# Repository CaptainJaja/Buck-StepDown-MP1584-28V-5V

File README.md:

# Buck Step-Down MP1584 – 28V vers 5V

Ce projet KiCad implémente un **convertisseur abaisseur (step-down)** basé sur le **MP1584**, capable de convertir une tension d'entrée allant jusqu'à **28V** en une sortie **stabilisée à 5V** avec un courant maximal de **3A**.

Le circuit imprimé a été conçu pour être **compact** et facile à intégrer, avec des dimensions de **24.5 mm × 28 mm**.

---

## 📷 Vues du PCB

### Face top (Top layer)

### Face bottom (Bottom layer)

---

## 📄 Datasheet

La **datasheet du MP1584** est disponible dans le répertoire sous le nom : `MP1584.PDF`

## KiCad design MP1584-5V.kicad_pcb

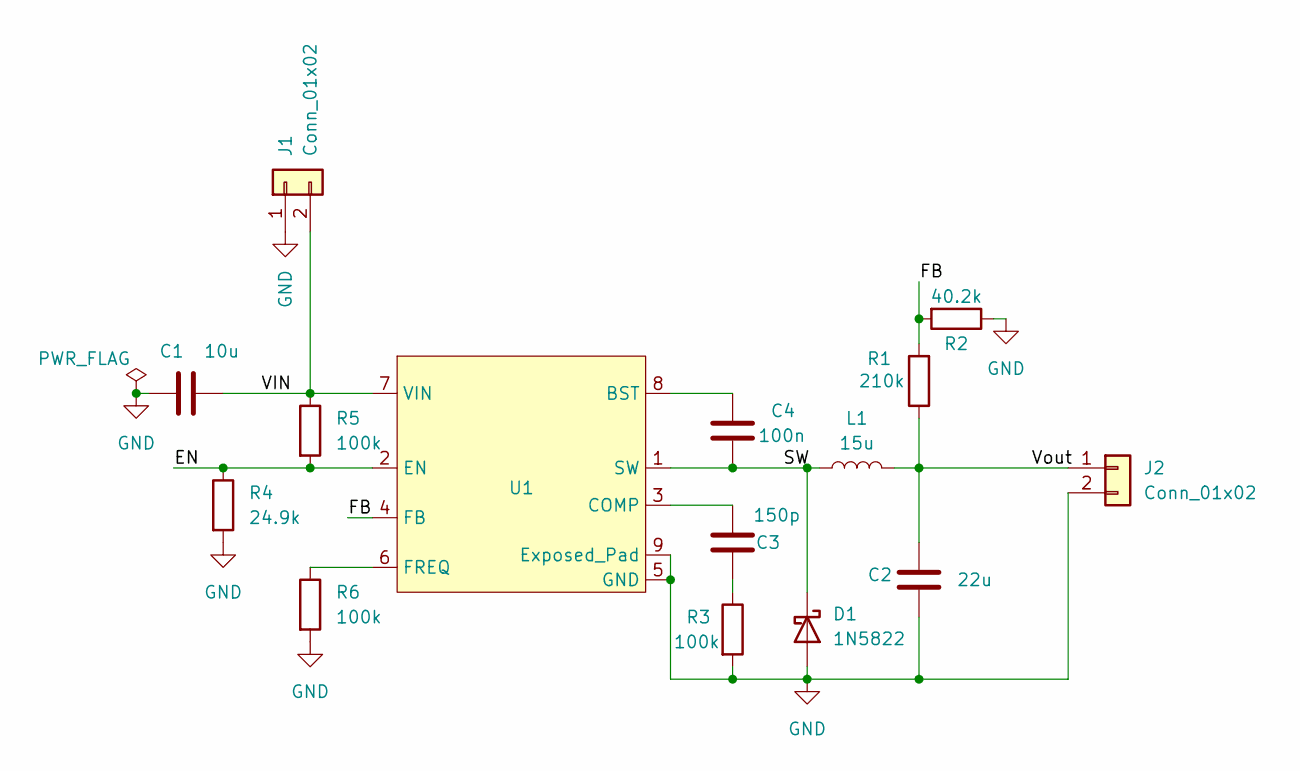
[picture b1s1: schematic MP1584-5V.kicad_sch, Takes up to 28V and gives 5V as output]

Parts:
C1: 10u; C_0603_1608Metric
C2: 22u; C_0805_2012Metric
C3: 150p; C_0603_1608Metric
C4: 100n; C_0603_1608Metric
D1: 1N5822; FSV330AF
J1, J2: Conn_01x02; JST_EH_S2B-EH_1x02_P2.50mm_Horizontal
L1: 15u; CDRH127F-150M
R1: 210k; R_0603_1608Metric
R2: 40.2k; R_0603_1608Metric
R3, R5, R6: 100k; R_0603_1608Metric
R4: 24.9k; R_0603_1608Metric
U1: MP1584-custom

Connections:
/EN: R4.1, R5.2, U1.2 (EN)
/FB: R1.2, R2.2, U1.4 (FB)
/SW: C4.2, D1.1 (K), L1.1, U1.1 (SW)
/VIN: C1.1, J1.2, R5.1, U1.7 (VIN)
/Vout: C2.1, J2.1, L1.2, R1.1
GND: C1.2, C2.2, D1.2 (A), J1.1, J2.2, R2.1, R3.2, R4.2, R6.2, U1.5 (GND), U1.9 (Exposed_Pad)
unnamed: C3.2, R3.1
unnamed: C4.1, U1.8 (BST)
unnamed: C3.1, U1.3 (COMP)
unnamed: R6.1, U1.6 (FREQ)

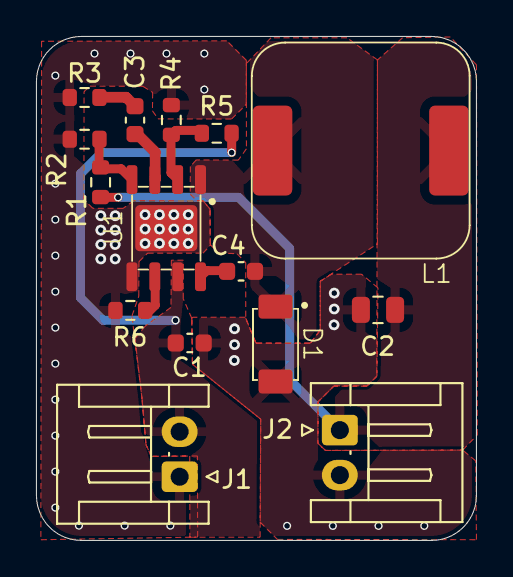
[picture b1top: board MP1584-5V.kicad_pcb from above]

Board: 2 copper layers, 24.4 x 28.0 mm, 15 parts (0 on the bottom side), 10 nets.

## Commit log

2025-05-07 Ajout du projet Kicad
2025-05-07 Finalisation PCB
2025-05-08 amélioration finale + modification des photos du README
2025-05-08 modif README
2025-05-08 ajout des fichiers Gerber
